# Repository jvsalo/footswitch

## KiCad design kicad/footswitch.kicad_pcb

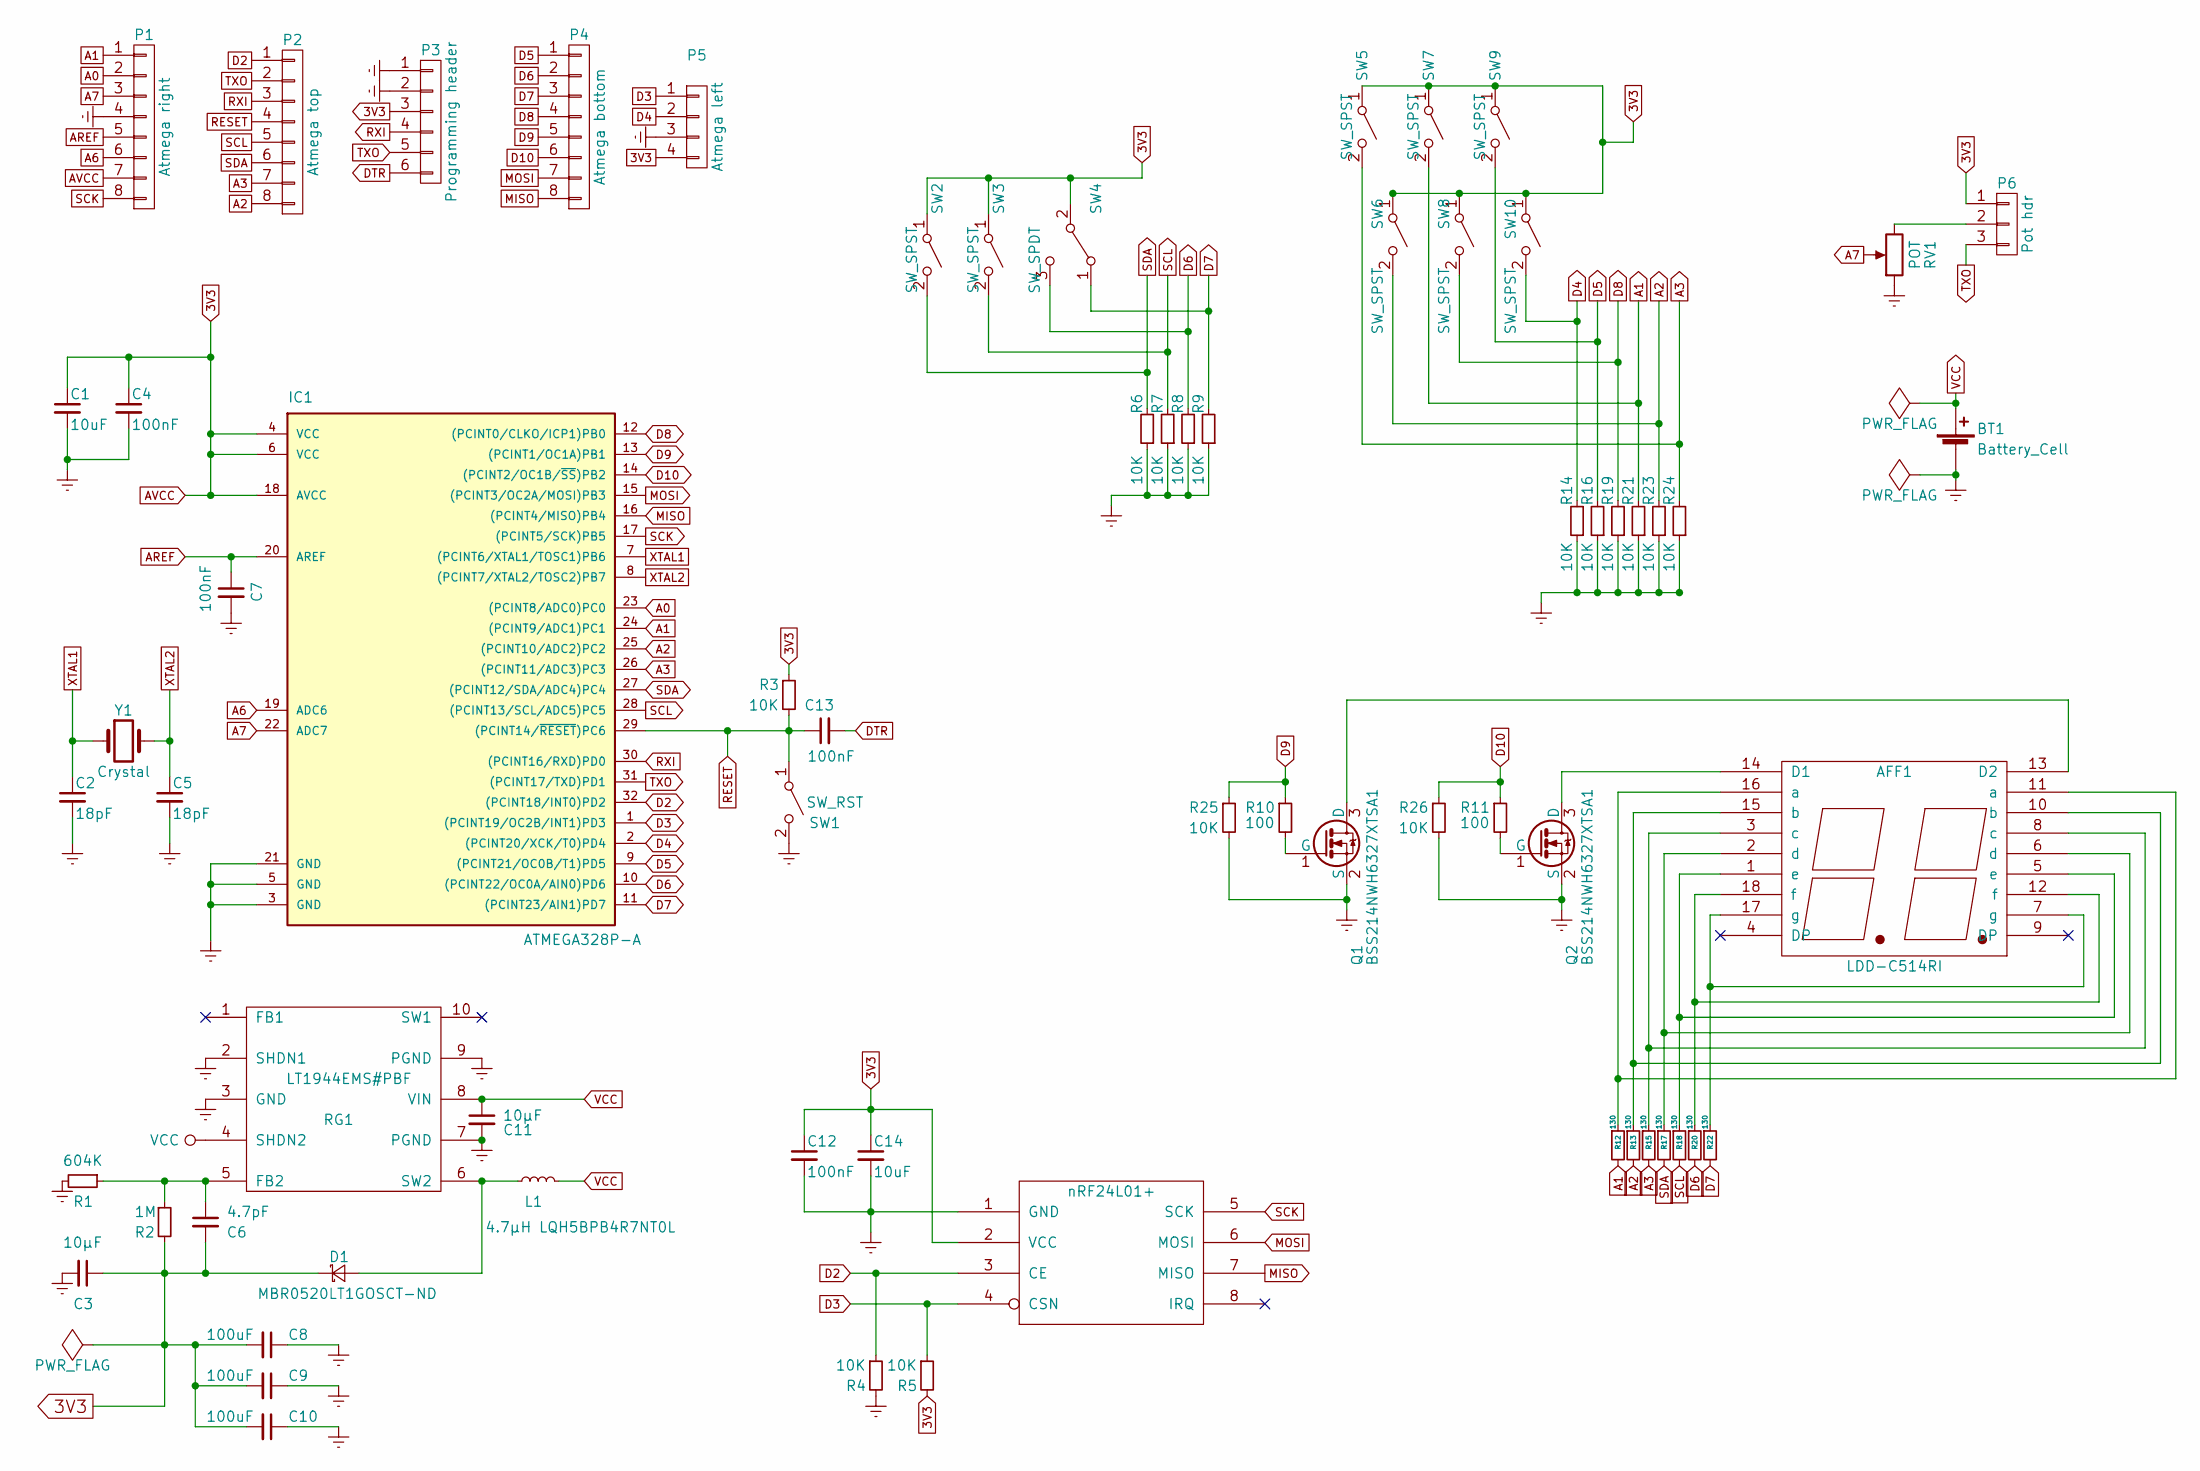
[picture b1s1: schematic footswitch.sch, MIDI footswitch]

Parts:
AFF1: LDD-C514RI; DA56
BT1: Battery_Cell; Pin_Header_Straight_1x02_Pitch2.54mm
C1, C14: 10uF; C_1206_HandSoldering
C2, C5: 18pF; C_1206_HandSoldering
C3, C11: 10µF; C_1206_HandSoldering
C4, C7, C12, C13: 100nF; C_1206_HandSoldering
C6: 4.7pF; C_1206_HandSoldering
C8, C9, C10: 100uF; C_1206_HandSoldering
D1: MBR0520LT1GOSCT-ND; D_SOD-123
IC1: ATMEGA328P-A; TQFP-32_7x7mm_Pitch0.8mm
L1: 4.7µH LQH5BPB4R7NT0L; Inductor_Taiyo-Yuden_NR-50xx_HandSoldering
P1: Atmega right; Pin_Header_Straight_1x08_Pitch2.54mm
P2: Atmega top; Pin_Header_Straight_1x08_Pitch2.54mm
P3: Programming header; Pin_Header_Straight_1x06_Pitch2.54mm
P4: Atmega bottom; Pin_Header_Straight_1x08_Pitch2.54mm
P5: Atmega left; Pin_Header_Straight_1x04_Pitch2.54mm
P6: Pot hdr; Pin_Header_Straight_1x03_Pitch2.54mm
Q1, Q2: BSS214NWH6327XTSA1; SOT-323_SC-70_Handsoldering
R1: 604K; R_1206_HandSoldering
R2: 1M; R_1206_HandSoldering
R3, R4, R5, R6, R7, R8, R9, R14, R16, R19, R21, R23, R24, R25, R26: 10K; R_1206_HandSoldering
R10, R11: 100; R_1206_HandSoldering
R12, R13, R15, R17, R18, R20, R22: 130; R_1206_HandSoldering
RG1: LT1944EMS#PBF; MSOP-10_3x3mm_Pitch0.5mm
RV1: POT; Pin_Header_Straight_1x03_Pitch2.54mm
SW1: SW_RST; SW_SPST_B3S-1000
SW2, SW3, SW5, SW6, SW7, SW8, SW9, SW10: SW_SPST; Pin_Header_Straight_1x02_Pitch2.54mm
SW4: SW_SPDT; Pin_Header_Straight_1x03_Pitch2.54mm
U1: nRF24L01+; NRF24L01
Y1: Crystal; Crystal_SMD_Abracon_ABM3-2pin_5.0x3.2mm_HandSoldering

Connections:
3V3: C1.1, C3.1, C4.1, C6.2, C8.2, C9.2, C10.2, C12.1, C14.1, D1.1 (K), IC1.4 (VCC), IC1.6 (VCC), IC1.18 (AVCC), P1.7, P3.3, P5.4, P6.1, R2.2, R3.1, R5.2, SW2.1 (A), SW3.1 (A), SW4.2 (B), SW5.1 (A), SW6.1 (A), SW7.1 (A), SW8.1 (A), SW9.1 (A), SW10.1 (A), U1.2 (VCC)
A0: IC1.23 ((PCINT8/ADC0)PC0), P1.2
A1: IC1.24 ((PCINT9/ADC1)PC1), P1.1, R12.2, R21.2, SW7.2 (B)
A2: IC1.25 ((PCINT10/ADC2)PC2), P2.8, R13.2, R23.2, SW6.2 (B)
A3: IC1.26 ((PCINT11/ADC3)PC3), P2.7, R15.2, R24.2, SW5.2 (B)
A6: IC1.19 (ADC6), P1.6
A7: IC1.22 (ADC7), P1.3, RV1.2
AREF: C7.1, IC1.20 (AREF), P1.5
D2: IC1.32 ((PCINT18/INT0)PD2), P2.1, R4.1, U1.3 (CE)
D3: IC1.1 ((PCINT19/OC2B/INT1)PD3), P5.1, R5.1, U1.4 (CSN)
D4: IC1.2 ((PCINT20/XCK/T0)PD4), P5.2, R14.2, SW10.2 (B)
D5: IC1.9 ((PCINT21/OC0B/T1)PD5), P4.1, R16.2, SW9.2 (B)
D6: IC1.10 ((PCINT22/OC0A/AIN0)PD6), P4.2, R8.2, R20.2, SW4.3 (C)
D7: IC1.11 ((PCINT23/AIN1)PD7), P4.3, R9.2, R22.2, SW4.1 (A)
D8: IC1.12 ((PCINT0/CLKO/ICP1)PB0), P4.4, R19.2, SW8.2 (B)
D9: IC1.13 ((PCINT1/OC1A)PB1), P4.5, R10.1, R25.1
D10: IC1.14 ((PCINT2/OC1B/~SS~)PB2), P4.6, R11.1, R26.1
DTR: C13.2, P3.6
Earth: BT1.2 (-), C1.2, C2.2, C3.2, C4.2, C5.2, C7.2, C8.1, C9.1, C10.1, C11.2, C12.2, C14.2, IC1.3 (GND), IC1.5 (GND), IC1.21 (GND), P1.4, P3.1, P3.2, P5.3, Q1.2 (S), Q2.2 (S), R1.2, R4.2, R6.1, R7.1, R8.1, R9.1, R14.1, R16.1, R19.1, R21.1, R23.1, R24.1, R25.2, R26.2, RG1.2 (SHDN1), RG1.3 (GND), RG1.7 (PGND), RG1.9 (PGND), RV1.1, SW1.2 (B), U1.1 (GND)
MISO: IC1.16 ((PCINT4/MISO)PB4), P4.8, U1.7 (MISO)
MOSI: IC1.15 ((PCINT3/OC2A/MOSI)PB3), P4.7, U1.6 (MOSI)
unnamed: AFF1.1 (e), AFF1.5 (e), R18.1
unnamed: AFF1.2 (d), AFF1.6 (d), R17.1
unnamed: AFF1.3 (c), AFF1.8 (c), R15.1
unnamed: AFF1.10 (b), AFF1.15 (b), R13.1
unnamed: AFF1.11 (a), AFF1.16 (a), R12.1
unnamed: AFF1.12 (f), AFF1.18 (f), R20.1
unnamed: AFF1.13 (D2), Q1.3 (D)
unnamed: AFF1.14 (D1), Q2.3 (D)
unnamed: AFF1.7 (g), AFF1.17 (g), R22.1
unnamed: C6.1, R1.1, R2.1, RG1.5 (FB2)
unnamed: D1.2 (A), L1.1, RG1.6 (SW2)
unnamed: P6.2, RV1.3
unnamed: Q1.1 (G), R10.2
unnamed: Q2.1 (G), R11.2
RESET: C13.1, IC1.29 ((PCINT14/~RESET~)PC6), P2.4, R3.2, SW1.1 (A)
RXI: IC1.30 ((PCINT16/RXD)PD0), P2.3, P3.4
SCK: IC1.17 ((PCINT5/SCK)PB5), P1.8, U1.5 (SCK)
SCL: IC1.28 ((PCINT13/SCL/ADC5)PC5), P2.5, R7.2, R18.2, SW3.2 (B)
SDA: IC1.27 ((PCINT12/SDA/ADC4)PC4), P2.6, R6.2, R17.2, SW2.2 (B)
TXO: IC1.31 ((PCINT17/TXD)PD1), P2.2, P3.5, P6.3
VCC: BT1.1 (+), C11.1, L1.2, RG1.4 (SHDN2), RG1.8 (VIN)
XTAL1: C2.1, IC1.7 ((PCINT6/XTAL1/TOSC1)PB6), Y1.1
XTAL2: C5.1, IC1.8 ((PCINT7/XTAL2/TOSC2)PB7), Y1.2

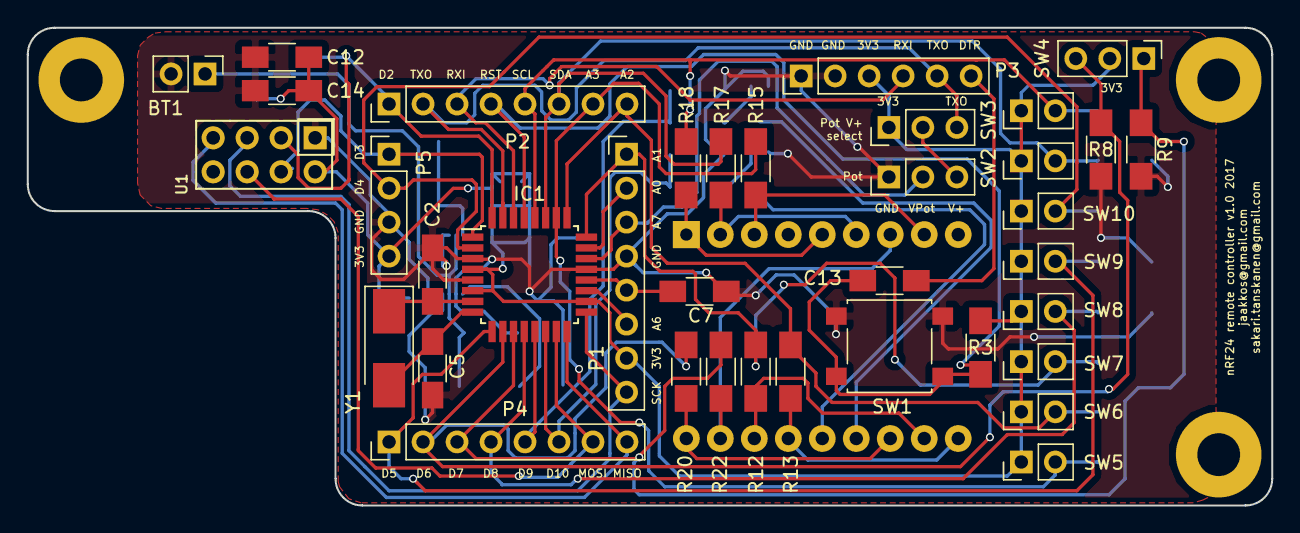
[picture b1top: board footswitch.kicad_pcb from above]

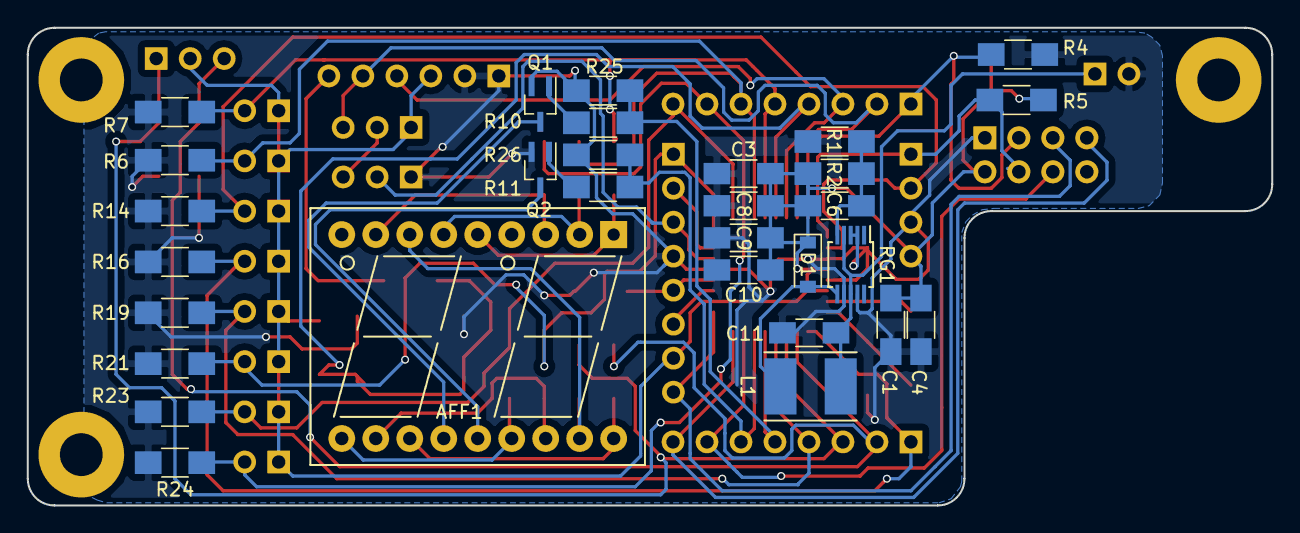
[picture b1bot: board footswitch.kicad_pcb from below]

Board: 2 copper layers, 93.0 x 35.7 mm, 67 parts (30 on the bottom side), 44 nets.

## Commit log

2017-04-11 Start schematic
2017-04-11 Add boost converter
2017-04-13 Continue schematic
2017-04-14 Add battery holder footprint
2017-04-14 Add radio footprints
2017-04-15 Finished schematic
    - finished schematic drawing
    - added schematic library for ldd-c514ri led display
    - added footprint for 100SP4T1B1M1QEH mom-off-mom switch
    - annotated footprints for components
2017-04-15 Fix CD4072BM96 footprint
2017-04-20 Fix bugs in schematic; start routing
2017-04-20 Continue routing
2017-04-21 Finish routing; markings and mounting still missing
2017-04-25 Remove OR gates; add version and authors to silk screen
2017-04-25 Move boost converter inductor away from under Atmega
2017-04-25 Add mounting holes
2017-04-26 Add silk screen markings
2017-05-01 Version 1.0
2017-05-25 Initial attempt at footswitch receiver code
2017-05-25 Misc. fixes
    - ADC6 and 7 have no digital IO on Atmega, change pins
    - Fix serial speed
    - Fix initialize printf library
2017-05-25 Fix whitespace and remove delay
2017-05-25 Misc. fixes
    - Add leading zeroes in hex printing
    - Set radio transfer rate
    - Fix message length and offset
2017-05-25 Fix MIDI optocoupler drive polarity
2017-05-26 Start footswitch firmware implementation
2017-05-26 Implement digits
2017-05-27 Add button interrupts and sleep code
2017-05-27 Misc. changes
    - Add potentiometer reading with deadzone and lowpass filtering
    - Export button state from button int handler
2017-05-27 Prevent ADC flapping
2017-05-27 Misc. changes
    - Implement automatic sleep after 10 second idle
    - Handle potentiometer button
    - Add blinking to potentiometer control mode
    - Increase potentiometer change threshold
2017-05-28 Add LED intensity control
2017-05-28 Handle button events in all modes
    Button actions are never omitted regardless of mode.
2017-05-28 Introduce preset state and fix race
2017-05-28 Implement button debounce
2017-05-28 Fade out LEDs before sleep
2017-05-28 Fix potentiometer dead zone
2017-05-28 Implement radio TX fail animation
2017-05-28 Misc. changes
    - Wait for potentiometer reading to converge
    - Implement volume and program change updates
2017-05-28 Try harder on RX fail; fix fail animation
2017-05-28 Fix code to use full 7-bit volume range
2017-05-28 Prevent radio spam
2017-05-28 Add radio sleep/wakeup commands
2017-05-28 Fix sleep code
    - Disable ADC, saves a lot of power
    - Properly unwind if sleep condition re-check fails
2017-05-29 Change resistor values to 1M to conserve power
2017-05-29 Use TX pin to power ADC
2017-05-30 Misc. changes
    - Display preset numbers like other MIDI controllers,
    ie. preset indexing starting from 1
    - Swap footswitch buttons to match current assembly
    - Change volume control to set the "hard" volume
2017-06-04 Add missing volatile qualifiers
2017-06-06 Fix serial_msg
